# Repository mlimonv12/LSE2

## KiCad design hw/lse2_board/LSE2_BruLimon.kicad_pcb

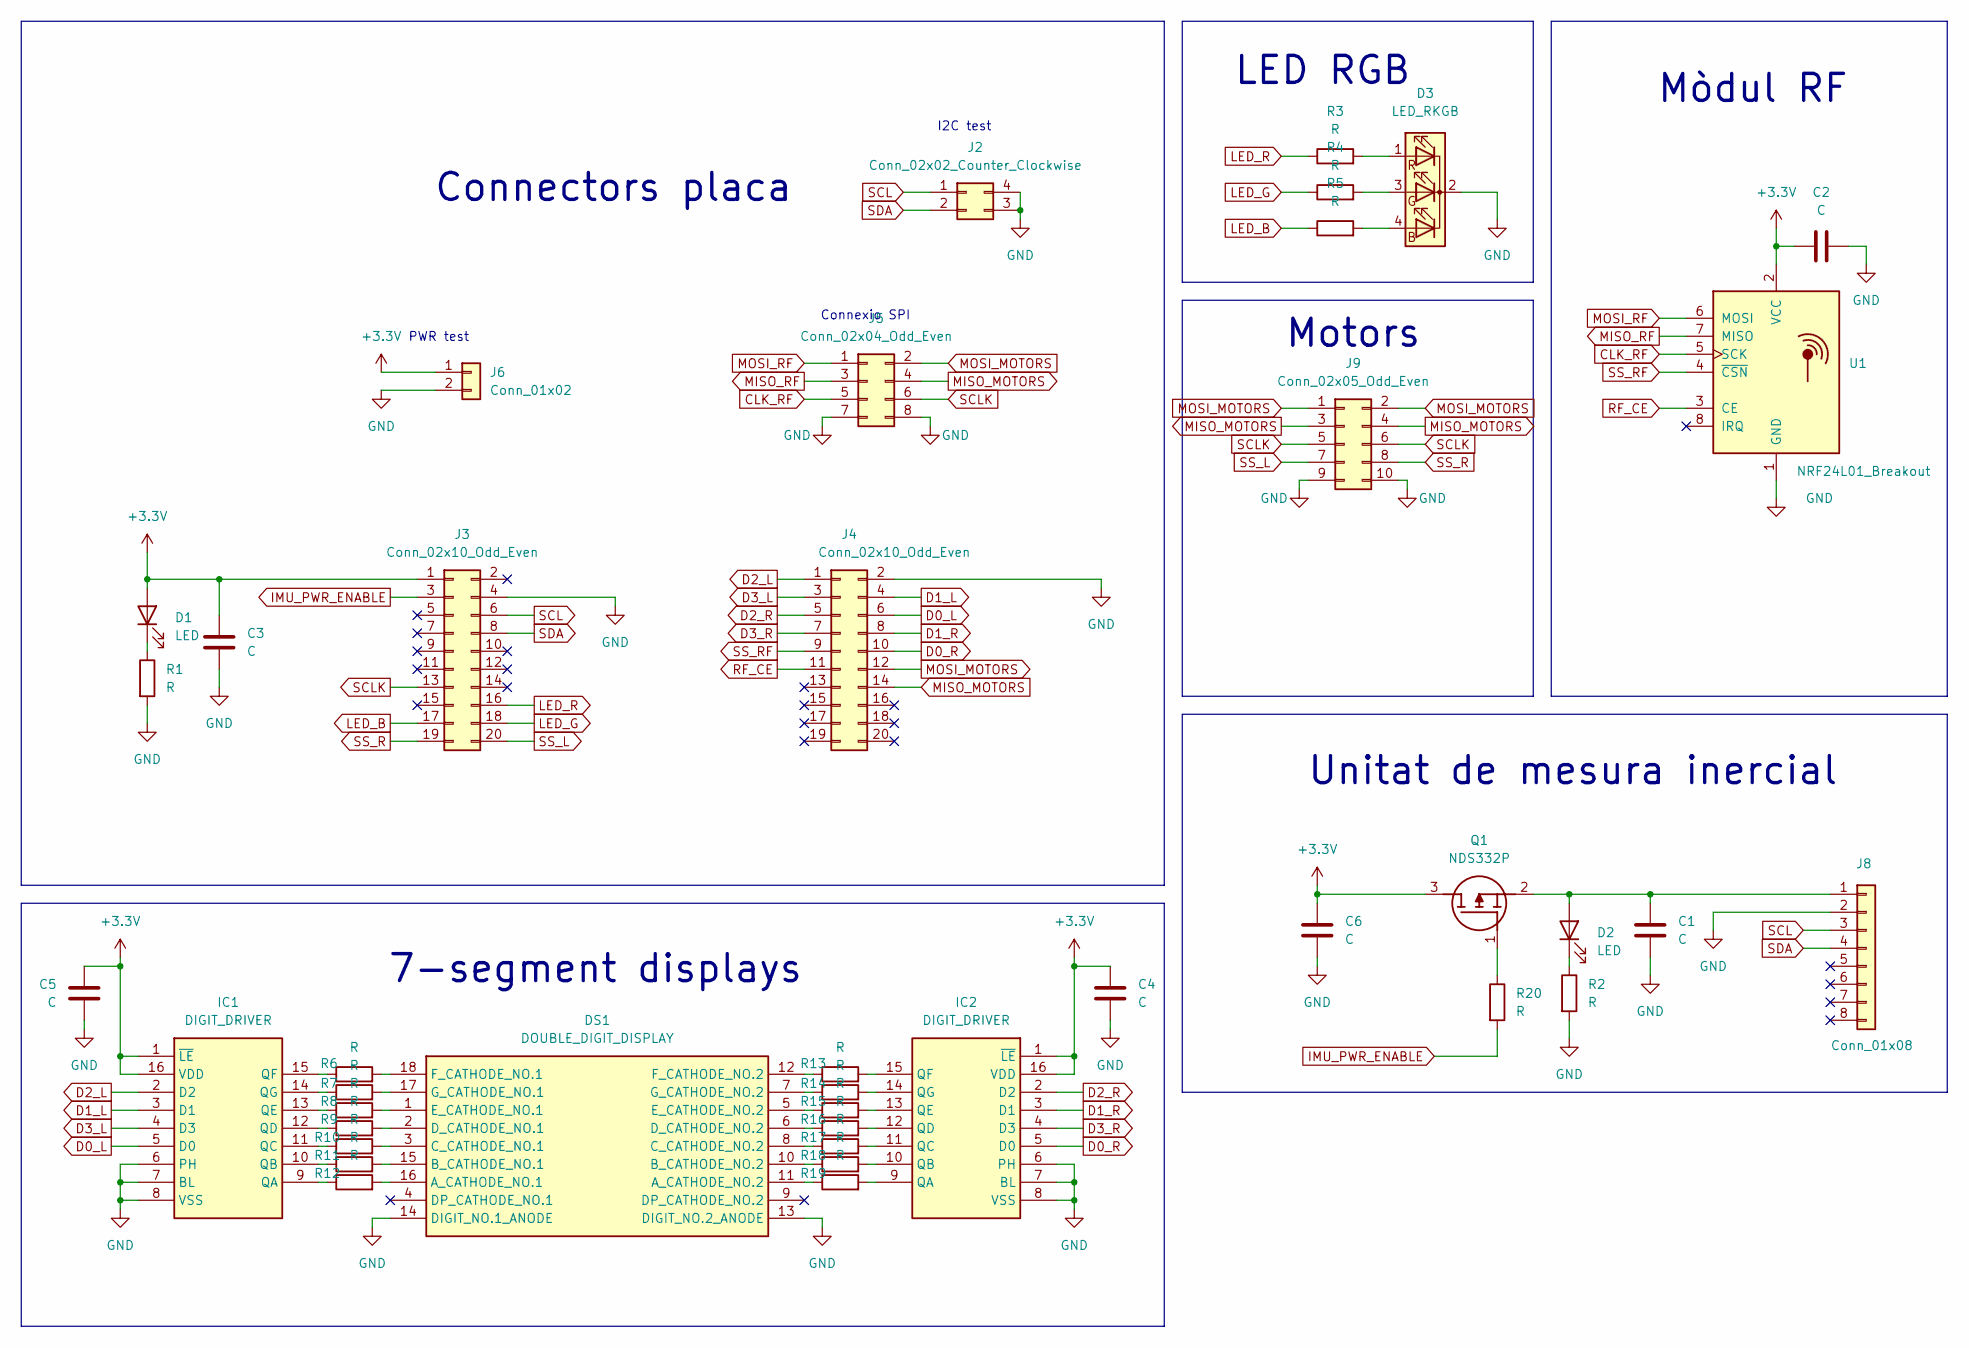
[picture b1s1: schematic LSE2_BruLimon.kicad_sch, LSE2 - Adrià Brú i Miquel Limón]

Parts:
C1, C2, C3, C4, C5, C6: C; C_1206_3216Metric
D1, D2: LED; LED_D3.0mm
D3: LED_RKGB; LED_D5.0mm-4_RGB
DS1: DOUBLE_DIGIT_DISPLAY; DA56-11CGKWA; Mouser Part Number 630-HDSP-521E
IC1, IC2: DIGIT_DRIVER; HEF4543BT653; Mouser Part Number 771-HEF4543BT653
J2: Conn_02x02_Counter_Clockwise; PinHeader_2x02_P2.54mm_Vertical
J3, J4: Conn_02x10_Odd_Even; PinHeader_2x10_P2.54mm_Vertical
J5: Conn_02x04_Odd_Even; PinHeader_2x04_P2.54mm_Vertical
J6: Conn_01x02; PinHeader_1x02_P2.54mm_Vertical
J8: Conn_01x08; GY-91
J9: Conn_02x05_Odd_Even; PinHeader_2x05_P2.54mm_Vertical
Q1: NDS332P; SuperSOT-3; Mouser Part Number 512-NDS332P
R1, R2, R3, R4, R5, R6, R7, R8, R9, R10, R11, R12, R13, R14, R15, R16, R17, R18, R19, R20: R; R_1206_3216Metric
U1: NRF24L01_Breakout; nRF24L01_Breakout

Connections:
+3.3V: C2.1, C3.1, C4.1, C5.1, C6.1, D1.2 (A), IC1.1 (~LE), IC1.16 (VDD), IC2.1 (~LE), IC2.16 (VDD), J3.1, J6.1, Q1.3 (D), U1.2 (VCC)
CLK_RF: J5.5, U1.5 (SCK)
D0_L: IC1.5 (D0), J4.6
D0_R: IC2.5 (D0), J4.10
D1_L: IC1.3 (D1), J4.4
D1_R: IC2.3 (D1), J4.8
D2_L: IC1.2 (D2), J4.1
D2_R: IC2.2 (D2), J4.5
D3_L: IC1.4 (D3), J4.3
D3_R: IC2.4 (D3), J4.7
GND: C1.2, C2.2, C3.2, C4.2, C5.2, C6.2, D3.2 (K), DS1.13 (DIGIT_NO.2_ANODE), DS1.14 (DIGIT_NO.1_ANODE), IC1.6 (PH), IC1.7 (BL), IC1.8 (VSS), IC2.6 (PH), IC2.7 (BL), IC2.8 (VSS), J2.3, J2.4, J3.4, J4.2, J5.7, J5.8, J6.2, J8.2, J9.9, J9.10, R1.2, R2.2, U1.1 (GND); also elsewhere on the board
IMU_PWR_ENABLE: J3.3, R20.2
LED_B: J3.17, R5.1
LED_G: J3.18, R4.1
LED_R: J3.16, R3.1
MISO_MOTORS: J4.14, J5.4, J9.3, J9.4
MISO_RF: J5.3, U1.7 (MISO)
MOSI_MOTORS: J4.12, J5.2, J9.1, J9.2
MOSI_RF: J5.1, U1.6 (MOSI)
unnamed: D1.1 (K), R1.1
unnamed: C1.1, D2.2 (A), J8.1, Q1.2 (S)
unnamed: D2.1 (K), R2.1
unnamed: D3.4 (BA), R5.2
unnamed: D3.3 (GA), R4.2
unnamed: D3.1 (RA), R3.2
unnamed: DS1.16 (A_CATHODE_NO.1), R12.2
unnamed: DS1.11 (A_CATHODE_NO.2), R19.1
unnamed: DS1.15 (B_CATHODE_NO.1), R11.2
unnamed: DS1.10 (B_CATHODE_NO.2), R18.1
unnamed: DS1.3 (C_CATHODE_NO.1), R10.2
unnamed: DS1.8 (C_CATHODE_NO.2), R17.1
unnamed: DS1.2 (D_CATHODE_NO.1), R9.2
unnamed: DS1.6 (D_CATHODE_NO.2), R16.1
unnamed: DS1.1 (E_CATHODE_NO.1), R8.2
unnamed: DS1.5 (E_CATHODE_NO.2), R15.1
unnamed: DS1.18 (F_CATHODE_NO.1), R6.2
unnamed: DS1.12 (F_CATHODE_NO.2), R13.1
unnamed: DS1.17 (G_CATHODE_NO.1), R7.2
unnamed: DS1.7 (G_CATHODE_NO.2), R14.1
unnamed: IC1.9 (QA), R12.1
unnamed: IC1.10 (QB), R11.1
unnamed: IC1.11 (QC), R10.1
unnamed: IC1.12 (QD), R9.1
unnamed: IC1.13 (QE), R8.1
unnamed: IC1.15 (QF), R6.1
unnamed: IC1.14 (QG), R7.1
unnamed: IC2.9 (QA), R19.2
unnamed: IC2.10 (QB), R18.2
unnamed: IC2.11 (QC), R17.2
unnamed: IC2.12 (QD), R16.2
unnamed: IC2.13 (QE), R15.2
unnamed: IC2.15 (QF), R13.2
unnamed: IC2.14 (QG), R14.2
unnamed: Q1.1 (G), R20.1
RF_CE: J4.11, U1.3 (CE)
SCL: J2.1, J3.6, J8.3; also elsewhere on the board
SCLK: J3.13, J5.6, J9.5, J9.6
SDA: J2.2, J3.8, J8.4; also elsewhere on the board
SS_L: J3.20, J9.7
SS_R: J3.19, J9.8
SS_RF: J4.9, U1.4 (~CSN)

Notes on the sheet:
Motors
Unitat de mesura inercial
Connectors placa
PWR test
Mòdul RF
LED RGB
I2C test
Connexio SPI
7-segment displays

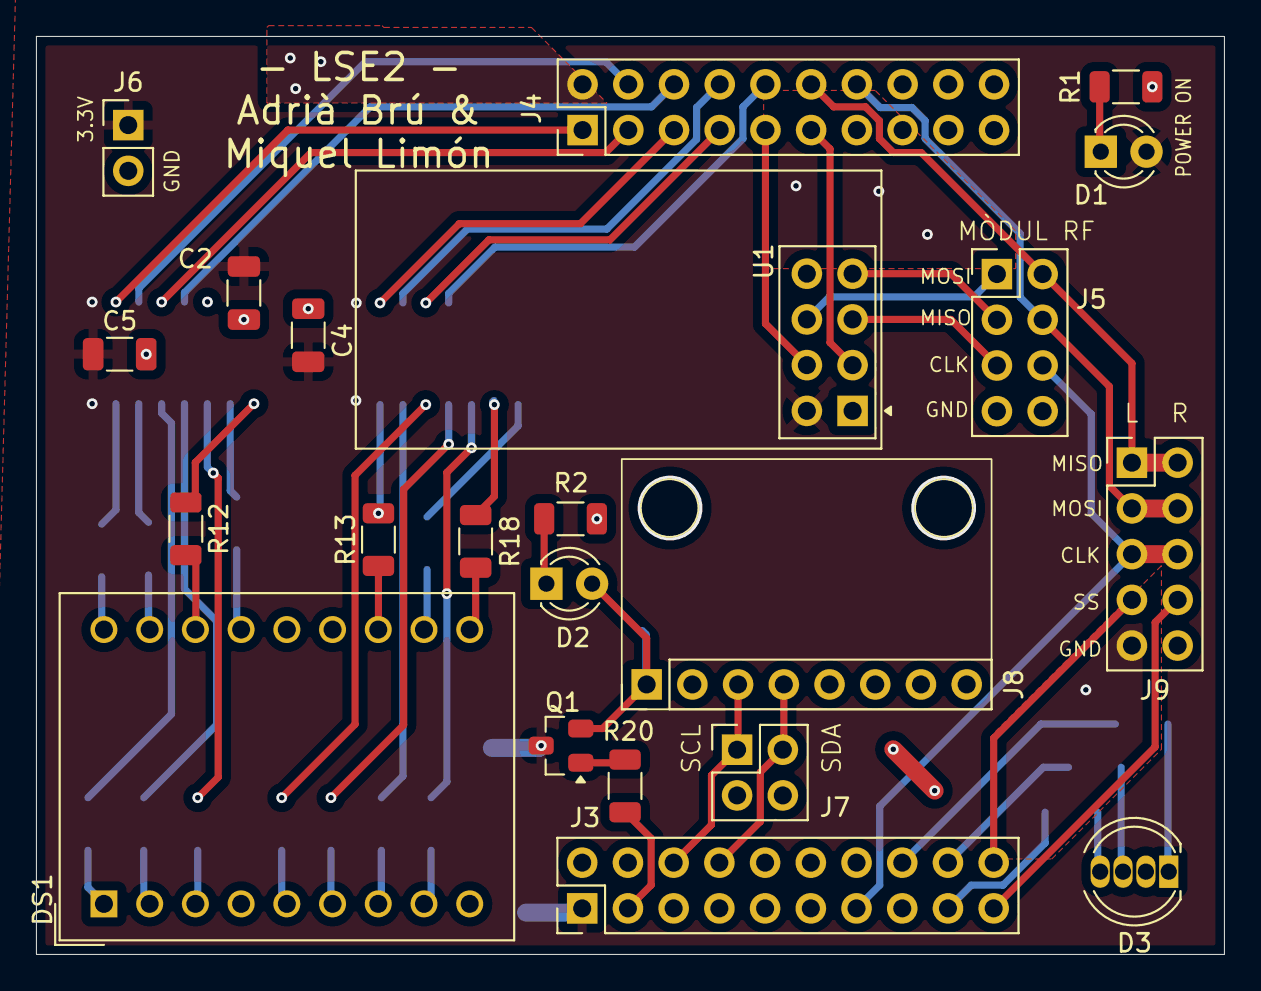
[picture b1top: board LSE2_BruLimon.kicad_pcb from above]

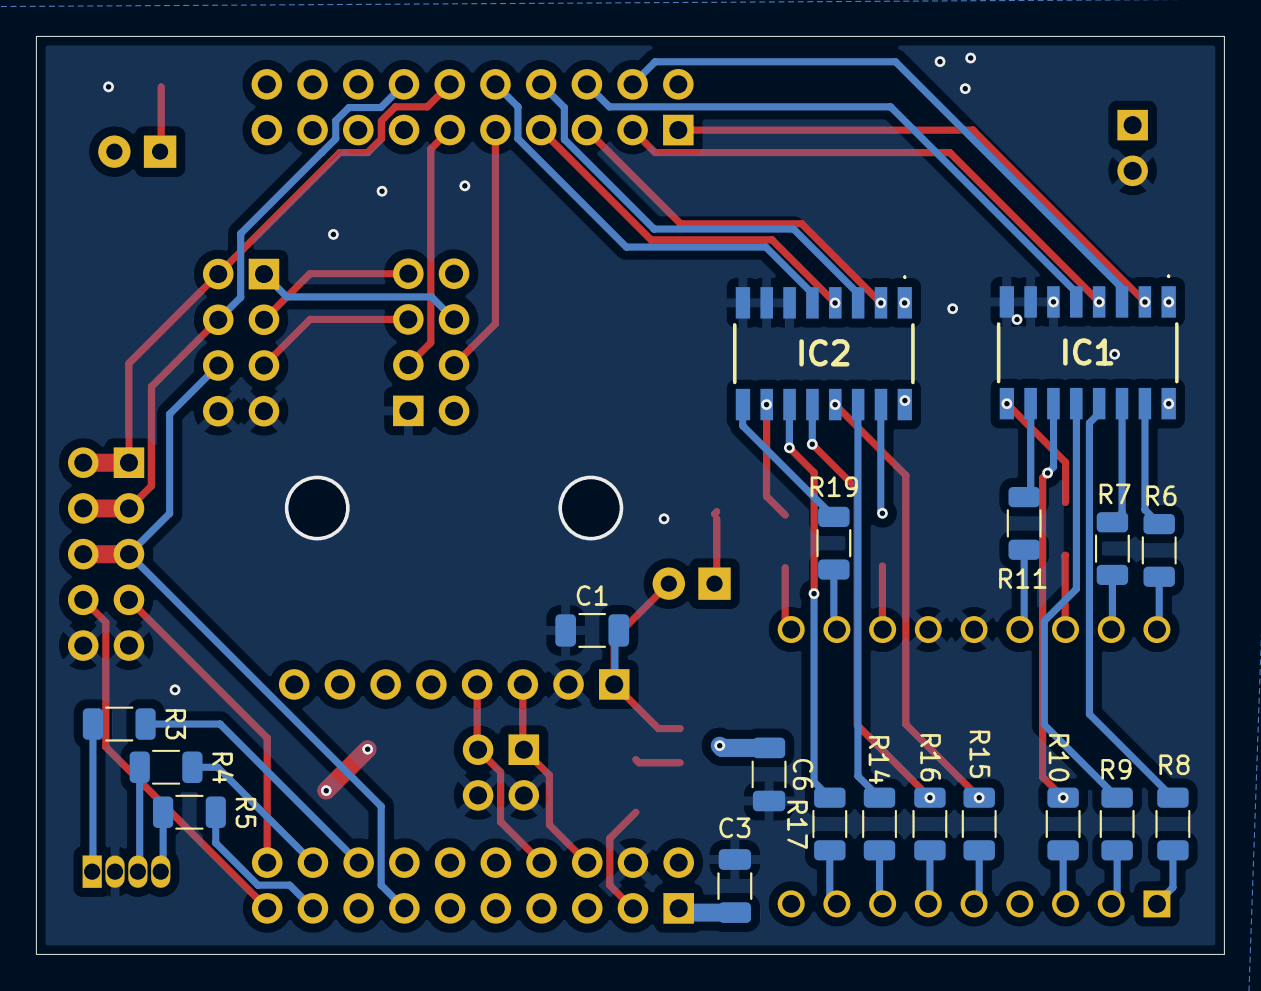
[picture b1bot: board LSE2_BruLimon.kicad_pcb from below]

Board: 2 copper layers, 66.0 x 51.0 mm, 41 parts (19 on the bottom side), 61 nets.

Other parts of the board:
J7: Conn_02x02_Counter_Clockwise; PinHeader_2x02_P2.54mm_Vertical

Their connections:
GND: J7.3, J7.4; also elsewhere on the board
SCL: J7.1; also elsewhere on the board
SDA: J7.2; also elsewhere on the board

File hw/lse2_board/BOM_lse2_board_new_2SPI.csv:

"Id";"Identificador";"Huella";"Cantidad";"Identificación";"Suministrador y ref";
1;"IC2,IC1";"HEF4543BT653";2;"DIGIT_DRIVER";;;
2;"J5";"PinHeader_2x04_P2.54mm_Vertical";1;"Conn_02x04_Odd_Even";;;
3;"J9";"PinHeader_2x05_P2.54mm_Vertical";1;"Conn_02x05_Odd_Even";;;
4;"C4,C5,C2,C6,C3,C1";"C_1206_3216Metric";6;"C";;;
5;"R12,R18,R20,R1,R13,R2,R6,R8,R16,R4,R9,R17,R14,R11,R7,R10,R5,R15,R19,R3";"R_1206_3216Metric";20;"R";;;
6;"D1,D2";"LED_D3.0mm";2;"LED";;;
7;"J4,J3";"PinHeader_2x10_P2.54mm_Vertical";2;"Conn_02x10_Odd_Even";;;
8;"Q1";"SuperSOT-3";1;"NDS332P";;;
9;"DS1";"DA56-11CGKWA";1;"DOUBLE_DIGIT_DISPLAY";;;
10;"U1";"nRF24L01_Breakout";1;"NRF24L01_Breakout";;;
11;"J8";"GY-91";1;"Conn_01x08";;;
12;"J7";"PinHeader_2x02_P2.54mm_Vertical";1;"Conn_02x02_Counter_Clockwise";;;
13;"J6";"PinHeader_1x02_P2.54mm_Vertical";1;"Conn_01x02";;;
14;"D3";"LED_D5.0mm-4_RGB";1;"LED_RKGB";;;

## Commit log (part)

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2025-08-15 disseny acabat v1
2025-08-15 disseny v1
2026-03-02 nova placa (cal revisar)
2026-03-04 placa abans d'entregar
2026-04-21 I2C fet, falta polir SPI i RTOS
2026-04-27 SPI fet + primera prova RTOS
2026-05-01 mes coses RTOS
2026-05-06 gitignore
2026-05-13 primers passos a RTOSitzacio
2026-05-13 rtosització completa
2026-05-20 stack overflow corregit but something is wrong
2026-06-15 15/6
2026-06-25 ultim dia
